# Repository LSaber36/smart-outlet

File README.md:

# smart-outlet
This repository is for a smart outlet project.
The smart-outlet will be able to read current and turn the outlet on and off.
Combining these basic inputs and outputs with features in the app, a user will have 
full control over the power they are using from the given outlet.

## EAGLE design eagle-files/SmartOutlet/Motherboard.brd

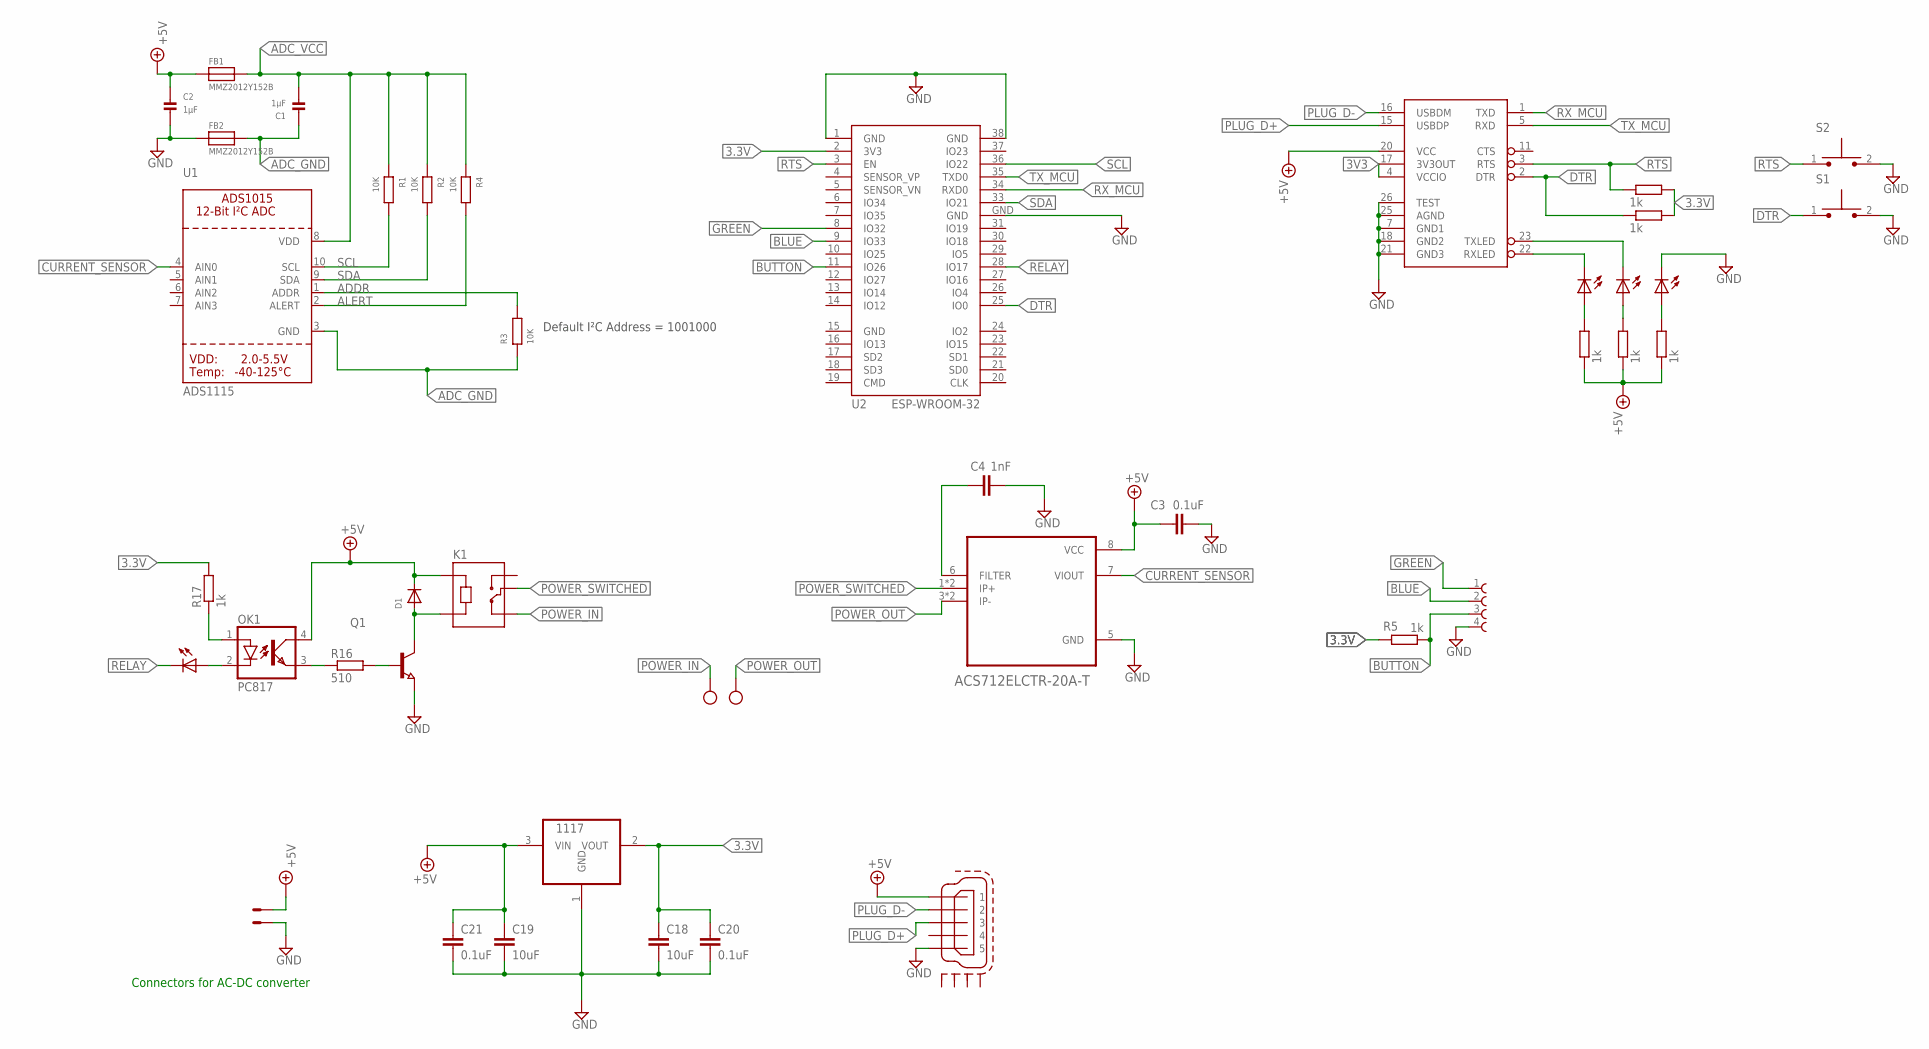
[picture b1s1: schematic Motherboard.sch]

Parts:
C1, C2: 1µF; 0805
C3, C20, C21: 0.1uF; 0603
C4: 1nF; 0603
C18, C19: 10uF; 1206
D1: DIODE_SOD-123FL; SOD-123FL
FB1, FB2: MMZ2012Y152B; 0805
IC1: 1117; SOT223
K1: SRD-05VDC-SL-C; RELAY_SRD-05VDC-SL-C
K2: 68610414122
OK1: PC817; DIL04
POWER_LED: LEDCHIP-LED0603; CHIP-LED0603
Q1: NPN-TRANSISTOR_SOT23; SOT23
R1, R2, R3, R4: 10K; R0603
R5, R7, R8, R9, R10, R11, R17: 1k; R0603
R16: 510; R0603
RELAY: LEDCHIP-LED0603; CHIP-LED0603
RX_LED: LEDCHIP-LED0603; CHIP-LED0603
S1, S2: TL1015AF160QG; SW_TL1015AF160QG
TX_LED: LEDCHIP-LED0603; CHIP-LED0603
U1: ADS1115; MSOP10
U2: ESP-WROOM-32
U3: FT232RL; SSOP28DB
U4: ACS712ELCTR-20A-T; SOIC127P600X175-8N
U$2: ZX62D-B-5P8
X1: W237-102
X2: 22-23-2021

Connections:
3.3V: C18.1, C20.1, IC1.2 (VOUT), R5.1, R8.2, R11.2, R17.2, U2.2 (3V3)
3V3: U3.4 (VCCIO), U3.17 (3V3OUT)
+5V: C2.1, C3.1, C19.1, C21.1, D1.C, FB1.1, IC1.3 (VIN), K1.A1, OK1.4 (COL), R7.1, R9.1, R10.1, U3.20 (VCC), U4.8 (VCC), U$2.P$1 (1), X2.1
ACS_FILTER: C4.1, U4.6 (FILTER)
ADC_GND: C1.1, FB2.2, R3.1, U1.3 (GND)
ADC_VCC: C1.2, FB1.2, R1.1, R2.1, R4.1, U1.8 (VDD)
ADDR: R3.2, U1.1 (ADDR)
ALERT: R4.2, U1.2 (ALERT)
BLUE: K2.2, U2.9 (IO33)
BUTTON: K2.3, R5.2, U2.11 (IO26)
CURRENT_SENSOR: U1.4 (AIN0), U4.7 (VIOUT)
DTR: R11.1, S1.1, U2.25 (IO0), U3.2 (DTR)
GND: C2.2, C3.2, C4.2, C18.2, C19.2, C20.2, C21.2, FB2.1, IC1.1 (GND), K2.4, POWER_LED.C, Q1.2 (E), S1.2, S2.2, U2.1 (GND), U2.15 (GND), U2.38 (GND), U2.GND, U3.7 (GND1), U3.18 (GND2), U3.21 (GND3), U3.25 (AGND), U3.26 (TEST), U4.5 (GND), U$2.P$5 (5), X2.2
GREEN: K2.1, U2.8 (IO32)
unnamed: OK1.2 (C), RELAY.A
unnamed: OK1.1 (A), R17.1
unnamed: R10.2, TX_LED.A
unnamed: OK1.3 (EMIT), R16.1
unnamed: Q1.1 (B), R16.2
unnamed: R9.2, RX_LED.A
PLUG_D+: U3.15 (USBDP), U$2.P$3 (3)
PLUG_D-: U3.16 (USBDM), U$2.P$2 (2)
POWER_IN: K1.NC, X1.1
POWER_LED: POWER_LED.A, R7.2
POWER_OUT: U4.3 (IP-), U4.4 (IP-), X1.2
POWER_SWITCHED: K1.COM, U4.1 (IP+), U4.2 (IP+)
RELAY: RELAY.C, U2.28 (IO17)
RELAY_GND: D1.A, K1.A2, Q1.3 (C)
RTS: R8.1, S2.1, U2.3 (EN), U3.3 (RTS)
RX_LED: RX_LED.C, U3.22 (RXLED)
RX_MCU: U2.34 (RXD0), U3.1 (TXD)
SCL: R1.2, U1.10 (SCL), U2.36 (IO22)
SDA: R2.2, U1.9 (SDA), U2.33 (IO21)
TX_LED: TX_LED.C, U3.23 (TXLED)
TX_MCU: U2.35 (TXD0), U3.5 (RXD)

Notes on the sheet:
Default I²C Address = 1001000
Connectors for AC-DC converter

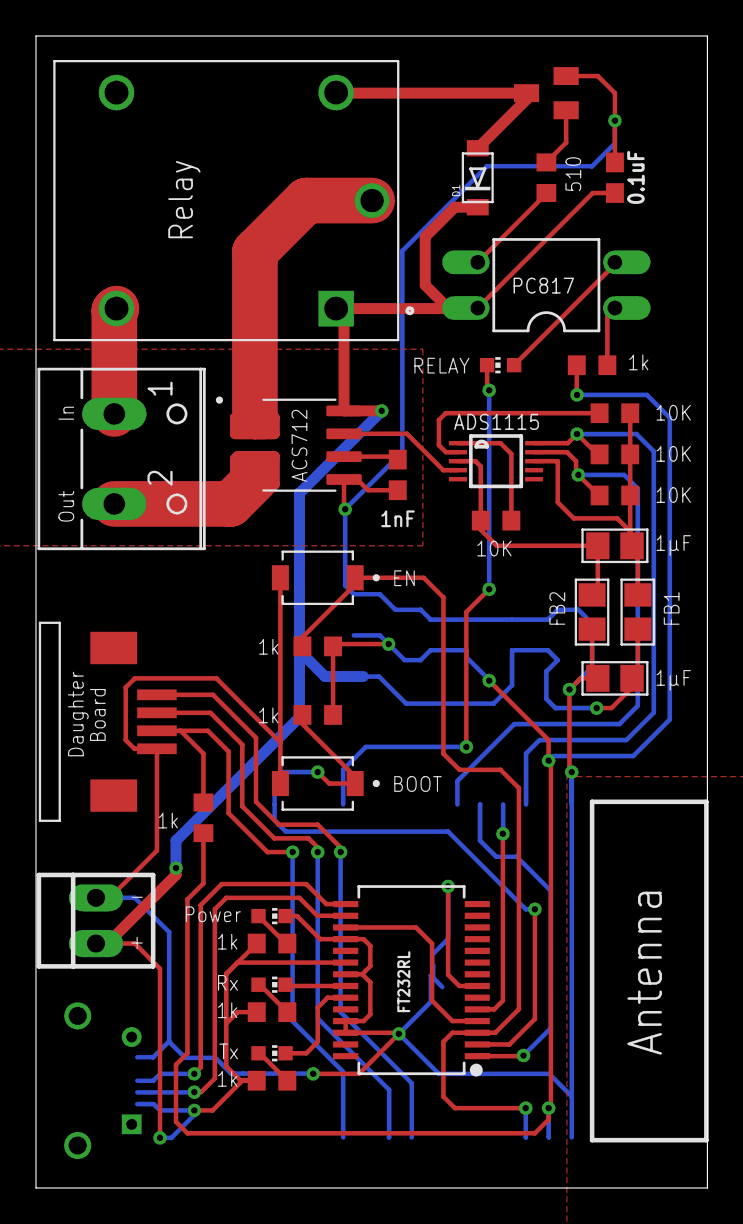
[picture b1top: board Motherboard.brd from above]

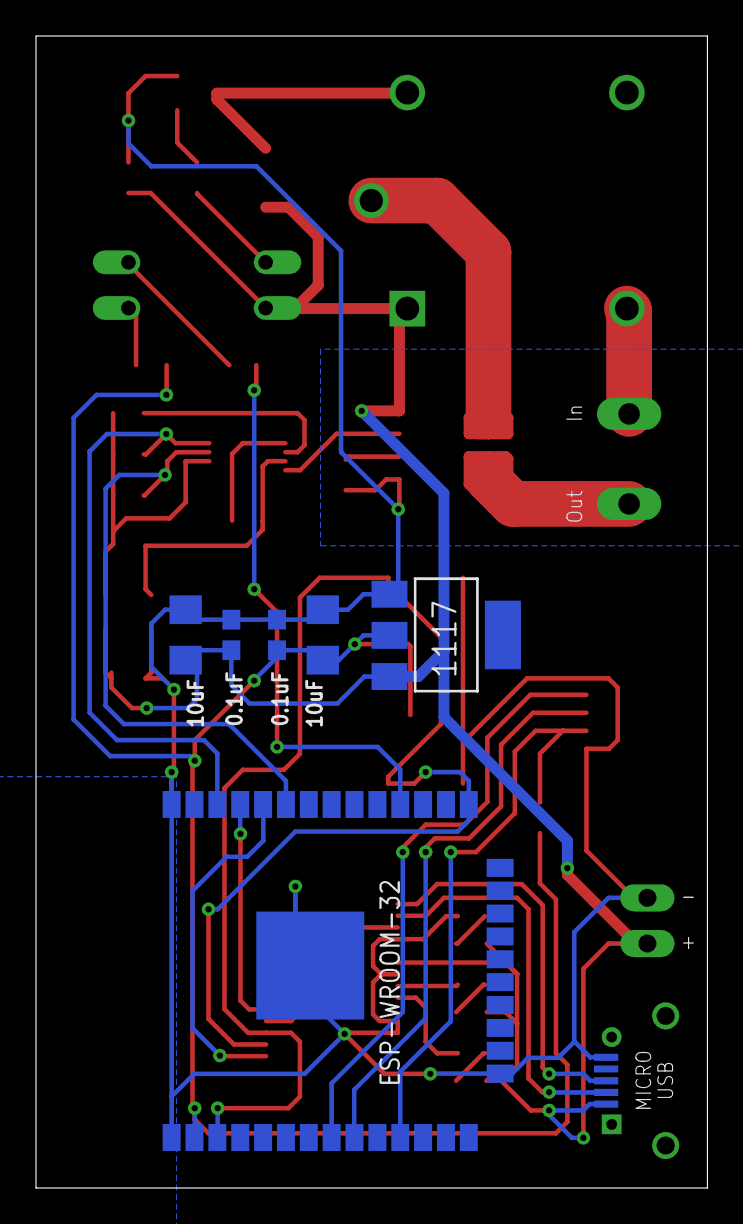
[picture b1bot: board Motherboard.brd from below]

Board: 2 copper layers, 37.3 x 64.0 mm, 41 parts (7 on the bottom side), 35 nets.

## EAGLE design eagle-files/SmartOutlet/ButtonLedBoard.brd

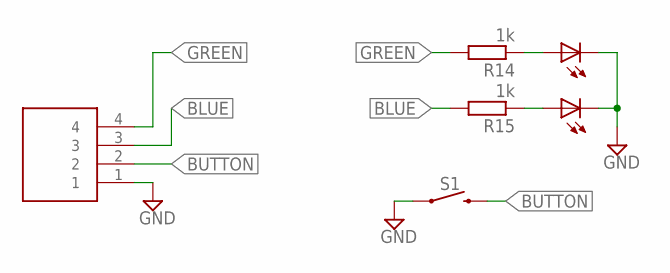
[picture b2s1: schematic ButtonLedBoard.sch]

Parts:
J1: 826629-4; TE_826629-4
LED1, LED2: LEDCHIP-LED0603; CHIP-LED0603
R14, R15: 1k; R0603
S1: MOMENTARY-SWITCH-SPST-SMD-6.0X3.5MM; TACTILE_SWITCH_SMD_6.0X3.5MM

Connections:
BLUE: J1.3, R15.2
BUTTON: J1.2, S1.2
GND: J1.1, LED1.C, LED2.C, S1.1
GREEN: J1.4, R14.2
unnamed: LED1.A, R14.1
unnamed: LED2.A, R15.1

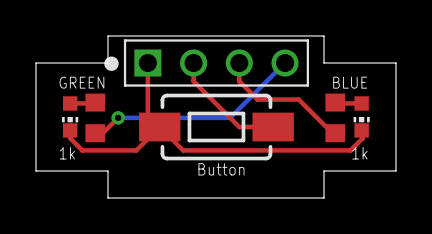
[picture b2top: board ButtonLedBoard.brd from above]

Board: 2 copper layers, 20.0 x 9.0 mm, 6 parts (0 on the bottom side), 6 nets.

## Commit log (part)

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2022-04-13 Setup basic file structure for repository
2022-04-13 Initial laptop commit
2022-04-13 Removed initial unused file
2022-04-13 Added figma link to app directory readme
2022-04-15 Setup linter settings
2022-04-19 Updated environment files
2022-04-19 Added basic template for each page
2022-04-21 Added router and basic navigation
2022-05-17 Added scrollview for devices
2022-05-18 Added button navigation to device page and data passing
2022-05-19 Removed comment due to using other gitignore file
2022-05-19 Added config file to gitignore for security purposes
2022-05-19 Removed unused import
2022-05-19 Updated code to send new variable names to Realtime database
2022-05-20 Integrated redux into project
2022-05-21 Replaced Realtime database with Firestore database
2022-05-21 Added check in case outlet id being parsed does not exist
2022-05-21 Added unsubscribe function to avoid unmounted screen parsing
2022-05-21 Updated code to add an outlet to a local list
2022-05-21 Added ability to add devices to Firestore and read list from Firestore
2022-05-22 Added ability to remove an outlet from your account
2022-05-22 Updated naming from device to outlet
2022-05-22 Updated formatting and code organization
2022-05-22 Added modal to signup page
2022-05-22 Added modal to login page
2022-05-22 Added modal to signup page as well
2022-05-22 Updated ESP32 code to work with Firestore, not Realtime database
2022-05-24 Added email input for password reset modal
2022-05-24 Update page formatting
2022-05-24 Updated styles
2022-05-24 Updated login and signup styles and error messages
2022-05-24 Commented out code that needs user auth verification to run
2022-05-31 Added sign-in / sign-out functionality to app
2022-05-31 Removed unused variable
2022-06-01 Added modal to confirm a user logout
2022-06-01 Updated code formatting
2022-06-01 Added user data section in settings page
2022-06-01 Updated functions from function type to arrow function type
2022-06-01 Updated dashboard page to display a message when no outlets in user's list
2022-06-02 Removed back buttons made unnecessary by nav bar
2022-06-02 Added display name to settings screen
2022-06-02 Added password reset email to login page
2022-06-05 Removed redundant intermediary array
2022-06-05 Added outletService file and updated comment in userService file
2022-06-05 Removed services directory since it is not needed
2022-06-06 Updated text size to prevent wrapping
2022-06-06 Updated outletID to selectedOutletID for clarity
2022-06-06 Moved addOutlet and removeOutlet to new outletServices file
2022-06-07 Centralized data to one object instead of multiple objects
2022-06-07 Updated unsubscriber calls and naming
2022-06-07 Updated function name
2022-06-07 Removed commented code
2022-06-07 Updated alignment of text and made component for info fields
2022-06-07 Updated and cleaned up log statements
2022-06-07 Updated page titles
2022-06-08 Fixed bug with profile picture when logging out
2022-06-09 Added button to toggle outlet state
2022-06-09 Moved firebase function to userServices file
2022-06-09 Updated naming convention for clarity
2022-06-09 Moved settings navigation button to nav bar as an icon
2022-06-09 Updated formatting in settings
2022-06-09 Added scrollView to settings screen
2022-06-09 Sorted outlet device list
2022-06-09 Updated outlets to use uuids instead of integers
2022-06-13 Updated arduino code to subscribe to changes in outlet state via realtime database
2022-06-13 Removed unnecessary toString calls since value was already a string
2022-06-13 Updated ID for testing
2022-06-15 Relay Function Working Current Sensor Function with ADS 1115 in progress
2022-06-17 Updated arduino code to work with codebase
2022-06-17 Removed unused include
2022-06-17 Added data averaging to ADC data calculation
2022-06-21 Moved function to more appropriate file
2022-06-21 Added button timer code
2022-06-21 Added if-statement to only change relayState if needed
2022-06-21 Updated textbox to not auto-capitalize first letter when entering text
2022-06-21 Removed accidentally comitted code since it's unfinished
2022-06-21 Updated print statements for readability
2022-06-23 Added updated eagle files
2022-06-24 Added new packages and updated bluetooth permissions
2022-06-25 Updated infobox component
2022-06-25 Added modal for adding a menu with dynamic indicators
2022-06-25 Updated error message case and variable name
2022-06-25 Added historical data to cloud firestore
2022-06-25 Updated ESP32 deviceID
2022-06-25 Added main functionality to addDevice modal
2022-06-25 Added disabled button style
2022-06-25 Updated addOutlet flow
2022-06-26 Updated chart to use historical data from database
2022-06-27 Updated code to dynamically update perent thresh based on the maximum value of the dataset
2022-06-27 Added setThreshold functionality to device modal, has small bugs
2022-06-28 Fixed bug with message validation and database updating
2022-06-28 Updated formatting
2022-06-28 Removed header from splash stack
2022-06-28 Removed data field from outlet entry in realtime database
2022-06-28 Moved buttons to inside of scrollview and increased size
2022-06-28 Updated textbox component implementation
2022-06-28 Updated button styles
2022-06-28 Consolidated code for dynamic modal rendering
2022-06-28 Updated string literals
2022-06-28 Updated console log statement for readability
2022-06-29 Fixed bugs and successfully set up bluetooth
2022-06-29 Consolidated modalContainer to styles.js
2022-06-29 Moved bluetooth implementation to bluetoothservices.js
2022-06-29 Updatedprint statements
2022-06-30 Updated app icon to custom one
2022-07-01 Added SVGs and added logo to splash screen
2022-07-01 Updated styling for InfoBox component and settings page
2022-07-01 Prevented app from turning to landscape mode
2022-07-01 Updated component for dynamic styling
2022-07-01 Further updated component
2022-07-01 Added logos to login/signup pages and scrollview to signup
2022-07-01 Added KeyboardAvoidingView to make user experience better
2022-07-01 Fixed bug with keyboard moving views
2022-07-01 Updated color for readability
2022-07-01 Fixed bug where new user cannot add devices
2022-07-02 Made warnings into logs
2022-07-02 Made logout button higher
2022-07-02 Updated add device styling
2022-07-02 Addition to previous commit
2022-07-05 Fixed bug with firebase not working
2022-07-06 Incorperated bluetooth code into main code
2022-07-06 Updated pinouts for eagle design
2022-07-08 Updated pins for routing
2022-07-08 Updated pinouts again
2022-07-08 Updated PCB design
2022-07-09 Updated dashboard page to handle bluetooh errors better
2022-07-09 Updated page state management to use constants
2022-07-09 Updated firmware to allow for entering pairing mode multiple times
2022-07-09 Added page state for scan timeout and fixed retry bug
2022-07-09 Updated icon and added enter wifi page
2022-07-09 Added enum for communication codes
2022-07-09 Added state to indicate incorrect password to the user
2022-07-10 Updated styles, including a spot for network name in ENTER_WIFI page
2022-07-10 Updated console logging for user device list for readability
2022-07-10 Updated code to print user auth data once for readability
2022-07-10 Updated 'Dispatched ref list' message in console
2022-07-10 Upudated login and signup pages to behave properly with keyboard
2022-07-10 Updated login and signup
2022-07-11 Added support for handling permission rejections
2022-07-11 Added functionality to find current network name and verify a password for it
2022-07-11 Updated bluetooth manager object name for clarity
2022-07-11 Changed timer blinking led to green instead of blue
2022-07-11 Updated misc android files
2022-07-11 Added functionality so canceling the modal will close the bluetooth connection
2022-07-11 Updtaed eagle files
2022-07-11 Added function to bluetoothServices to send multiple values in an array
2022-07-11 Increased amount of time until the scanForOutlet function times out
2022-07-11 Removed subscribe function and updated sendMultiple
2022-07-12 Changed addOutlet to use a new UUID, not make one internally
2022-07-12 Updated bluetooth codes and set up responses to received commands
2022-07-12 Updated to use bluetooth after wifi validated, and receive bluetooth callbacks
2022-07-12 Updated log printing for clarity
2022-07-12 Updated log statement for readability
2022-07-12 Updated newline log statement]
2022-07-12 Added framework for evalulating network status based on incoming data
2022-07-12 Set errors for user and added statement to prevent repeating bluetooth actions
2022-07-14 Added code to store received valued in flash memory and respond to wifi connection status
2022-07-14 Added code to interact with flash memory storage and print information with button presses for testing
2022-07-14 Updated code to only connect to wifi and firebase on boot if information is saved in flash memory
2022-07-14 Added completion page to indicate successful action
2022-07-14 Added more pages for user information
2022-07-14 Added new states for handling certain codes received over ble
2022-07-14 Added space for readability
2022-07-14 Updated code to reboot device after connection is extablisted
2022-07-14 Moved firebase status update for safety
2022-07-14 Removed test button code for setting values in flash memory
2022-07-14 Added support for short multi button press
2022-07-15 Updated Current Sensor function -Changed to ADS1015 -Added new variables to Smart Outlet for ads reading:maxv,minv, counter -Changed current sensor fuinction from measuring average to finding min and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
2022-07-15 Fixed things to account for new Current sensor code
2022-07-16 Updated message for clarity
2022-07-16 Added support for pressing button to change state. Required separating firebase and bluetooth with different boot modes
2022-07-16 Removed unused variable causing runtime error
2022-07-16 Added timeout feature for connecting to wifi
2022-07-16 Updated timeout function to return truth about connection status
2022-07-16 Fixed bug with asynchronous data sending, pending optimization
2022-07-16 Added delay to make firebase sync correctly on reboot
2022-07-18 Removed unnecessary commented code
2022-07-18 Removed unused styles
2022-07-18 Added abillity to exit pairing mode when in it
2022-07-18 Fixed button lag problem and optimized ADC performance
2022-07-19 Updated function to work on different machines
2022-07-19 Moved powerThreshold to realtime database for app
2022-07-19 Updated loading message for clarity
2022-07-19 Added dynamic labels
2022-07-20 Added horizontal scrolling to graph for expandability and readability
2022-07-20 Removed trailing spaces
2022-07-20 Updated to set moethod to ensure correct update type on esp32
2022-07-20 Removed x-axis lable rotation
2022-07-20 Updated code to properly initialize variables on boot
2022-07-20 Updated new outlet initialization
2022-07-20 Updated code so relay pin state is set properly on initialization
2022-07-20 Updated android files from apk bundeling
2022-07-20 Added ability to perform an action every minute and every 5 minutes, which has a max response time of 3 seconds
2022-07-21 Fixed graph display bug
2022-07-21 Updated android file during debug apk generation
2022-07-21 Updated indexing for 24 hour time to 0-23
2022-07-21 Added historicalData reset function
2022-07-21 Removed test call from code
2022-07-21 Added power pointer and calculation
2022-07-21 power pointer added and caluctation
2022-07-21 Updated functions with filler code and updated print statements
2022-07-21 Added function to get time at current index in case of power outage
2022-07-21 Updated code to update internet-dependent viariables after firebase connection is established
2022-07-21 Added ADC and historicalData function calls to timer code
2022-07-21 Updated state datapath variable to be centralized to a global variable
2022-07-21 Commented out current print functions
2022-07-21 Updated code to properly update variable and cumSum
2022-07-22 Updated code to properly turn outlet off if outlet power threshold has been exceeded

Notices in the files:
parts and their libraries:
SparkFun-Switches: Licensing: Creative Commons ShareAlike 4.0 International - https://creativecommons.org/licenses/by-sa/4.0
esp32: Creative Commons Attribution-ShareAlike 4.0 International
4_pin_smd_connector: Copyright: Würth Elektronik
